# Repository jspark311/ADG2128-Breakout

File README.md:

# ADG2128-Breakout

A breakout board for Analog Devices' 8x12 analog cross-point switch.

#### [Hackaday.io Page](https://hackaday.io/project/167228-adg2128-breakout)

#### [Order from Tindie](https://www.tindie.com/products/17864/)

#### [Arduino driver](https://github.com/jspark311/Arduino-ADG2128)

------------------------

### What is in this repository:

**./doc**:  Location for documentation

**./KiCAD**:  Hardware design files

------------------------

Front | Back
:-------:|:------:
  |

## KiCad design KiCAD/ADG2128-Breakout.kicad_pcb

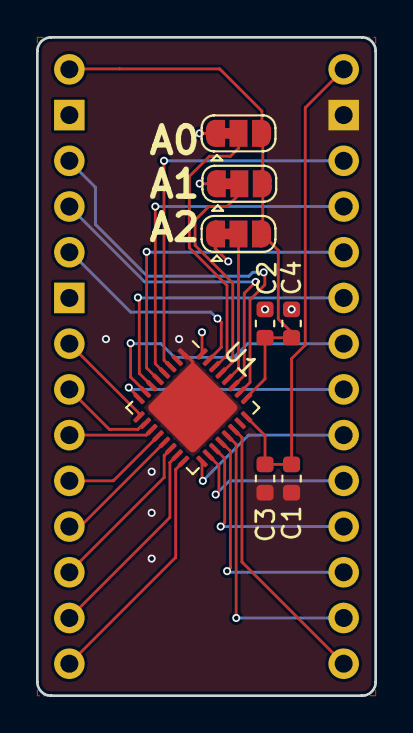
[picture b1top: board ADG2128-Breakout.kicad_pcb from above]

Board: 2 copper layers, 18.8 x 36.6 mm, 10 parts (0 on the bottom side), 30 nets.

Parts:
C1, C2, C3, C4: 1uF; C_0603_1608Metric
J1, J2: Conn_01x14_Male; PinHeader_1x14_P2.54mm_Vertical
J3, J4, J5: Conn_01x03_Male; SolderJumper-3_P1.3mm_Bridged12_RoundedPad1.0x1.5mm
U1: ADG2128; QFN-32-1EP_5x5mm_P0.5mm_EP3.65x3.65mm

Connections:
/A0: J3.2, U1.28
/A1: J4.2, U1.29
/A2: J5.2, U1.30
/ANAGND: C1.2, C3.2, J2.2, U1.1, U1.33
/ANAVcc: C1.1, C3.1, J2.1, U1.24
/GND: C2.2, C4.2, J1.2, J1.6, J3.1, J4.1, J5.1, U1.32
/SCL: J1.4, U1.27
/SDA: J1.3, U1.26
/Vcc: C2.1, C4.1, J1.1, J3.3, J4.3, J5.3, U1.25
/X0: J2.3, U1.3
/X1: J2.4, U1.4
/X2: J2.5, U1.5
/X3: J2.6, U1.6
/X4: J2.7, U1.7
/X5: J2.8, U1.8
/X6: J2.9, U1.17
/X7: J2.10, U1.18
/X8: J2.11, U1.19
/X9: J2.12, U1.20
/X10: J2.13, U1.21
/X11: J2.14, U1.22
/Y0: J1.7, U1.9
/Y1: J1.8, U1.10
/Y2: J1.9, U1.11
/Y3: J1.10, U1.12
/Y4: J1.11, U1.13
/Y5: J1.12, U1.14
/Y6: J1.13, U1.15
/Y7: J1.14, U1.16
/~RESET: J1.5, U1.31

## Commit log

2019-08-21 Adding hardware, and updating README.
2019-08-21 Updating README.
2019-08-21 Adding arduino boilerplate and an unported driver.
2019-08-28 Arduino driver updated.
2019-09-13 Fixing silk mistake.
2019-09-13 Publishing revised OshPark link and render.
2019-09-14 Update gitignore.
2019-11-19 Ooops. Wrong address in example conf.
2019-11-25 More fixes to driver.
2019-11-25 Driver now updates shadow registers on successful write.
2019-11-25 Finished example sketch. Verifies working. Last stage of cruft removal.
2019-11-26 Minor fix in example sketch to prevent confusion over i2c pins.
2019-11-30 Adding (de)serialization support. Private bools consolidated.
2019-11-30 Serialize safety. Unserialize exposed.
2019-11-30 Bus is now passed in as parameter it init().
2019-11-30 Updating documentation.
2019-12-02 Minor revisions for better manufacturability.
2019-12-02 Fix for bug causing reset() to return wrong result.
2019-12-04 Minor fix for a small logical gap on init.
2019-12-04 Documentation.
2019-12-04 Fixes for linux build.
2019-12-05 Clarity improvements.
2019-12-08 Now using StringBuilder for debugging output. Isolated by preprocessor flag.
2019-12-16 Filling out API. Breaking change to getValue(). Name never made sense.
2020-02-22 Arduino driver is now in the Library manager.
